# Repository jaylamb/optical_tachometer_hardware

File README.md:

# Optical Tachometer Hardware

The `optical_tachometer_hardware` project consists of a single printed circuit board (PCB)
which contains a TCRT5000 reflective sensor and its supporting circuitry. The device's
physical interface is a three position right-angle pin header.

## Usage
Built-up hardware is a sensor module designed to be interfaced with a General Purpose
Input/Output (GPIO) pin on a microcontroller. The sensor is active-high, and asserts its
output when in close proximity to a reflective object.

## License [Apache 2.0](http://www.apache.org/licenses/)

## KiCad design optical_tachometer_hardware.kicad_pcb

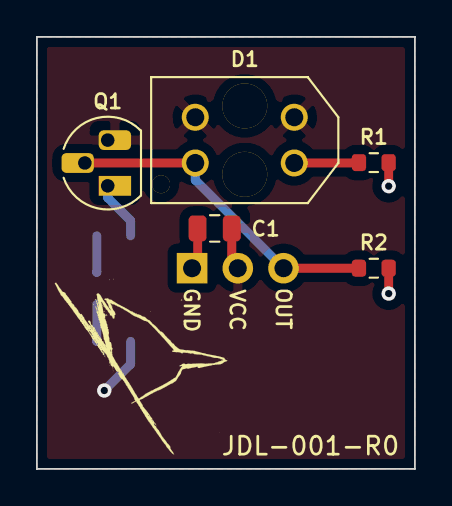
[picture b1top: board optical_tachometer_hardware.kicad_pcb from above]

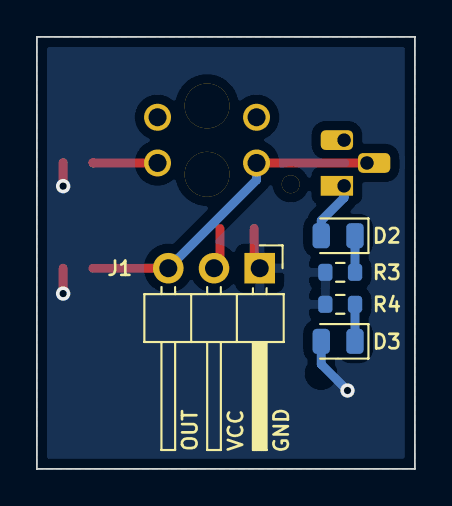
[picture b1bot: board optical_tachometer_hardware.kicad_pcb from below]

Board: 2 copper layers, 21.0 x 24.0 mm, 10 parts (5 on the bottom side), 7 nets.

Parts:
C1: 0.1uF; C_0805_2012Metric
D1: TCRT5000; tcrt5000
D2: GREEN; LED_0805_2012Metric
D3: BLUE; LED_0805_2012Metric
J1: J1; PinHeader_1x03_P2.54mm_Horizontal
Q1: 2N2222; TO-92_HandSolder
R1: 100; R_0603_1608Metric
R2: 10k; R_0603_1608Metric
R3, R4: 330; R_0603_1608Metric

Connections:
GND: C1.2, J1.1, R1.2, R2.2, R3.2, R4.2
unnamed: D1.4, R1.1
unnamed: D2.1, R3.1
unnamed: D2.2, Q1.1
unnamed: D3.1, R4.1
SENSOR_OUTPUT: D1.3, J1.3, Q1.2, R2.1
VCC: C1.1, D1.1, D1.2, D3.2, J1.2, Q1.3

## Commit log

2020-06-25 Add project CHANGELOG
    Supports #1.
2020-06-25 Make document title all caps
    Supports #1.
2020-09-29 Add KiCad project to repository
    Supports #3.
2020-09-29 Update CHANGELOG
    Supports #3.
2020-09-29 Add README to project
    Supports #2.
2020-09-29 Update CHANGELOG
    Supports #2.
2020-10-30 Add install and pre-commit hooks to project.
    Supports #8.
2020-10-30 Update CHANGELOG.
    Supports #8.
2020-10-30 Update project name in Git scripts
    Supports #8.
2020-10-30 Add official KiCad utilities as submodule
    Submodule placed in 'utility' directory. Directory ignored by
    pre-commit hook.
    Supports #9.
2020-10-30 Update CHANGELOG
    Supports #9.
2020-10-30 Correct spacing
    Supports #9.
2020-11-04 Add personal parts library as a submodule to this project
    Supports #13.
2020-11-10 Removed submodule kicad-library-utils
2020-11-10 Add kicad-library-utils repository as submodule (in the right place)
    Supports #13.
2020-11-10 Add KiAuto project as a submodule
    Supports #15.
2020-11-11 Add ERC to pre-commit hook
    Add empty schematic file to project.
    Add .gitignore to project, ignoring library caches.
    Supports #15.
2020-11-11 Add DRC to pre-commit hook
    Add empty layout file to project.
    Update .gitignore (backups, caches)
    Supports #15.
2020-11-30 Update parts library submodule
2020-12-11 Add schematic to project
    Add official footprint and symbol repositories as submodules.
    Add project specific footprint and symbol tables.
    Update pre-commit hook to ignore schematic files.
    Supports #4.
2020-12-14 Update personal parts library submodule
    Supports #5.
2020-12-14 Add all hardware to layout file
    Supports #5.
2021-01-12 Complete initial layout
    Supports #5.
2021-01-12 Add silk (logo, number) to pcb
    Supports #5.
2021-01-12 Update directory for TRCT5000 3D model
    footprint's default directory is <proj>/3d_models.
    Supports #5.
2021-01-12 Add descriptive silk
    Reduce size (1.0->0.8) of silk text
    Reduce silk thickness (0.20->0.15)
    Supports #5.
2021-01-16 Add InteractiveHtmlBom project as submodule
    Supports #18.
2021-01-16 Update project netlist
    Supports #18.
2021-01-16 Add PCB revision to layout file
    Revision (0), matches revision in schematic.
    PCB revision is used by BOM generation submodule.
    Supports #18.
2021-01-16 Add deliverables generation script
    Add interactive BOM generation to deliverables generation script.
    Add generated deliverables (BOM) to project repository.
    Supports #18.
2021-01-19 Update CHANGELOG
    Supports #23.
2021-01-19 Update README
    Supports #22.
2021-01-19 Update README, add figure
    Supports #22.
2021-03-28 Add new 100 ohm resistor to project, replacing the ERJ-3EKF1000V
    Supports #26.
